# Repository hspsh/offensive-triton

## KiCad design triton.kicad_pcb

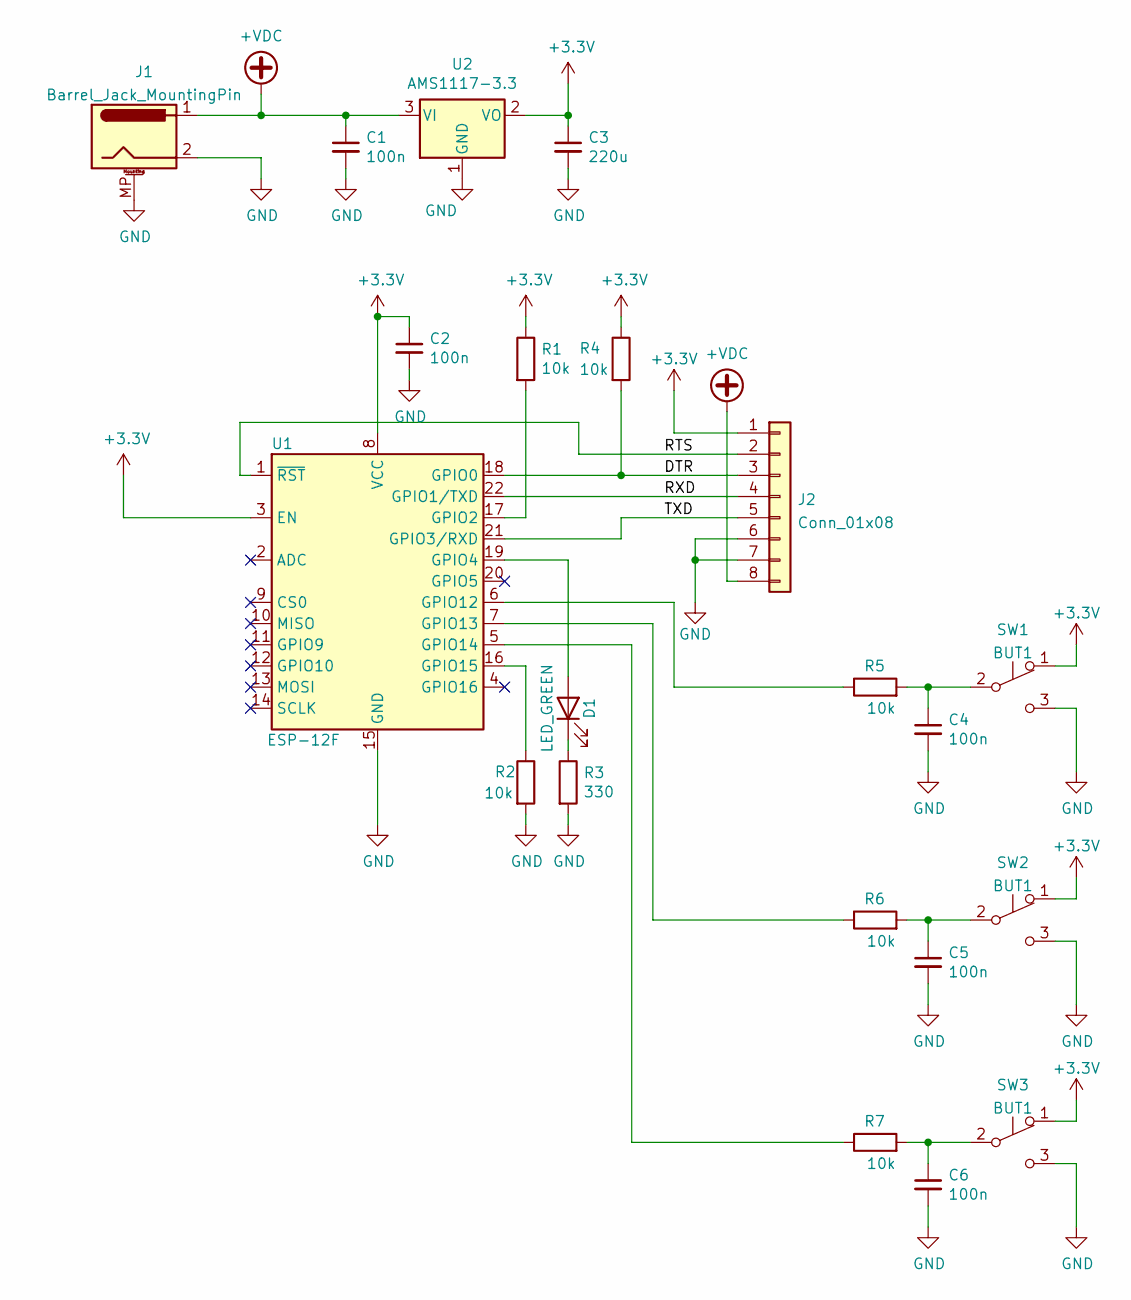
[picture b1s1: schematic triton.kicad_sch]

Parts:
C1, C2, C4, C5, C6: 100n; C_Disc_D7.5mm_W5.0mm_P5.00mm
C3: 220u; C_Radial_D8.0mm_H7.0mm_P3.50mm
D1: LED_GREEN; LED_D3.0mm
J1: Barrel_Jack_MountingPin; USB_C_Cursed
J2: Conn_01x08; PinHeader_1x08_P2.54mm_Vertical
R1, R2, R4, R5, R6, R7: 10k; R_Axial_DIN0207_L6.3mm_D2.5mm_P10.16mm_Horizontal
R3: 330; R_Axial_DIN0207_L6.3mm_D2.5mm_P10.16mm_Horizontal
SW1, SW2, SW3: BUT1; Cherry_DC3
U1: ESP-12F; ESP-12E
U2: AMS1117-3.3; SOT-223-3_TabPin2

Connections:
+3V3: C2.1, C3.1, J2.1, R1.1, R4.1, SW1.1 (A), SW2.1 (A), SW3.1 (A), U1.3 (EN), U1.8 (VCC), U2.2 (VO)
+VDC: C1.1, J1.1, J2.8, U2.3 (VI)
/DTR: J2.3, R4.2, U1.18 (GPIO0)
/RTS: J2.2, U1.1 (~RST)
/RXD: J2.4, U1.22 (GPIO1/TXD)
/TXD: J2.5, U1.21 (GPIO3/RXD)
GND: C1.2, C2.2, C3.2, C4.2, C5.2, C6.2, J1.2, J1.MP (MountPin), J2.6, J2.7, R2.2, R3.2, SW1.3 (C), SW2.3 (C), SW3.3 (C), U1.15 (GND), U2.1 (GND)
unnamed: C4.1, R5.2, SW1.2 (B)
unnamed: C5.1, R6.2, SW2.2 (B)
unnamed: C6.1, R7.2, SW3.2 (B)
unnamed: D1.1 (K), R3.1
unnamed: D1.2 (A), U1.19 (GPIO4)
unnamed: R1.2, U1.17 (GPIO2)
unnamed: R2.1, U1.16 (GPIO15)
unnamed: R5.1, U1.6 (GPIO12)
unnamed: R6.1, U1.7 (GPIO13)
unnamed: R7.1, U1.5 (GPIO14)

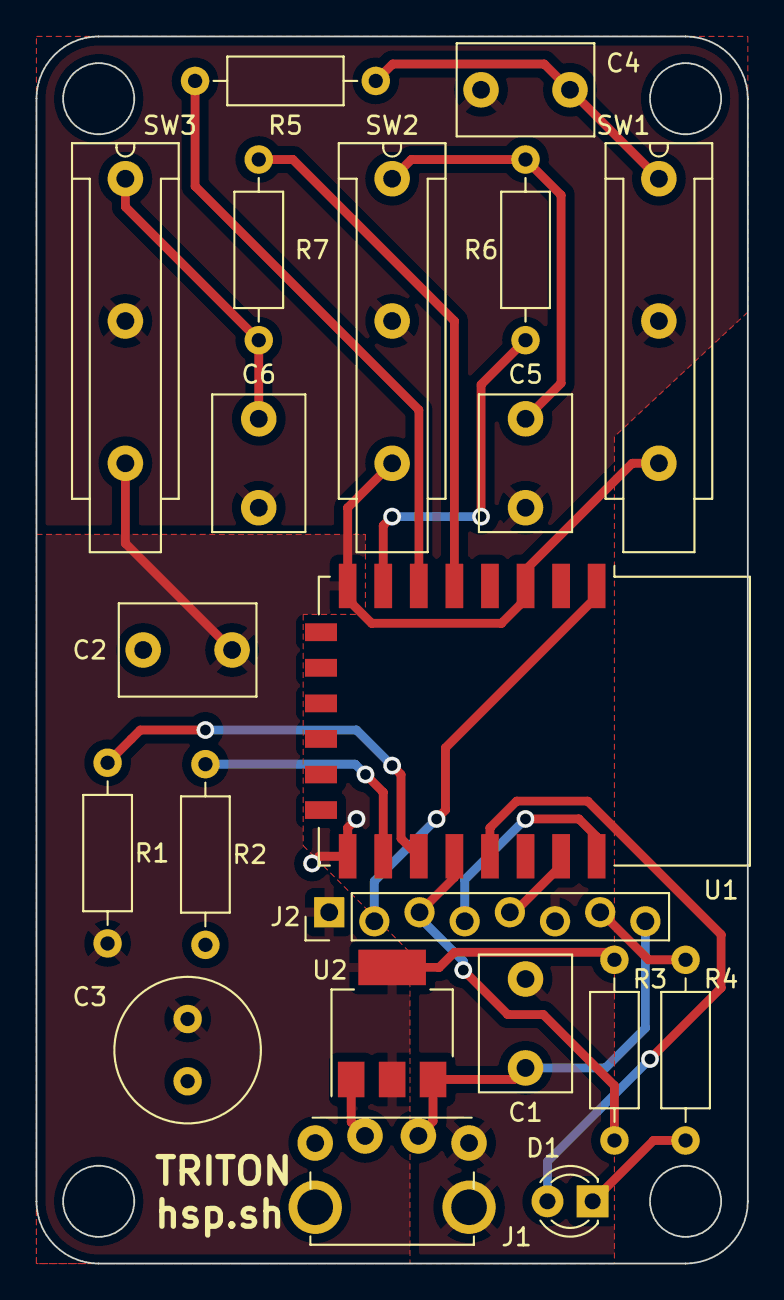
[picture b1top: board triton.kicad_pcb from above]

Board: 2 copper layers, 40.0 x 69.0 mm, 21 parts (0 on the bottom side), 17 nets.

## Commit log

2022-03-06 repo init
2022-03-06 adding fab outputs
2022-03-21 adding schematic
